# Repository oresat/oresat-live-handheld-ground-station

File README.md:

# Introduction
The OreSat Live Handheld Ground Station (HGS) project provides everything you need to build your own ground station capable of receiving images transmitted from OreSat in Low Earth Orbit.  HGS is designed to be inexpensive, easy to assemble, and simple to use so that it can be built by Middle and High School students.  The entire design is open source to encourage reuse and experimentation.

HGS is a portable unit built around a high gain directional antenna. Using a mobile phone application to locate OreSat, you aim the antenna to get the best possible signal. The live images are then received by the groundstation, error corrections are applied and the image is made available to any WiFi capable device through a built-in web page.

OreSat HGS act as a wifi access point providing an unsecured wireless network named "OreSatLive".  Devices identify the network as a hotspot requiring the user to sign-in for Internet access.  To view the image stream simply:
1. Connect your wifi to the "OreSatLive" network
2. Choose to sign-in when prompted
3. The OreSat Live web interface will open automatically

HGS was created for use with the OreSat mission, but it is designed to be used by any group interested in long range image transmission.  The handheld ground stations can be reused for other cubesat or balloon launches.

Once the final design is completed, users will be able to purchase all of the required parts as a kit from https://www.crowdsupply.com/

# HGS Parts List
All of the required parts to build HGS can be found in the Bill of Materials [(BOM)](BOM.md)

# Hardware Setup
Build your Handheld Ground Station kit according to the [Assembly Instructions](hgs-model/assembly-instructions/OreSat_Live_HGS_Assembly.pdf)

# Software Setup
1. [Download the SD card image oresat_hgs_14_jun_2019.img](https://drive.google.com/a/pdx.edu/uc?id=1BvP8ltkEwoBRSbCfQXceEiuxpVhkSf37&export=download)
2. Write the SD card image to a 2GB or larger card.  The [Raspberry Pi documentation](https://www.raspberrypi.org/documentation/installation/installing-images/) explains the procedure.

# Startup Procedure
1. Install the SD card in Raspberry Pi
2. Insert phone into the holder
3. Connect Raspberry Pi power cable to the USB power bank
4. Load Satellite AR app on phone and select OreSat
5. Point the ground station in the direction of OreSat
3. Connect your viewing devices to the "OreSatLive" wifi network

# Design Details
## Software Design
If you would like to build the software system from source follow the [Build Instructions](software/BUILD.md)

## Mechanical Design
You can 3D print all of the [mechanical parts](hgs-model/README.md)  

## Circuit Board Design
The integrated antenna backplane and matching network [circuit board design files](backplane/README.md)

# Related Projects
[OreSat Live](https://github.com/oresat/oresat-dxwifi-software) for software and firmware used on OreSat satellite

[Mini OreSat](https://github.com/oresat/oresat-live-mini-oresat) combines the OreSat Live software with a Raspberry Pi Zero W + Pi Camera to create platform for hobbyist and classroom experiments with high-altitude ballooning.

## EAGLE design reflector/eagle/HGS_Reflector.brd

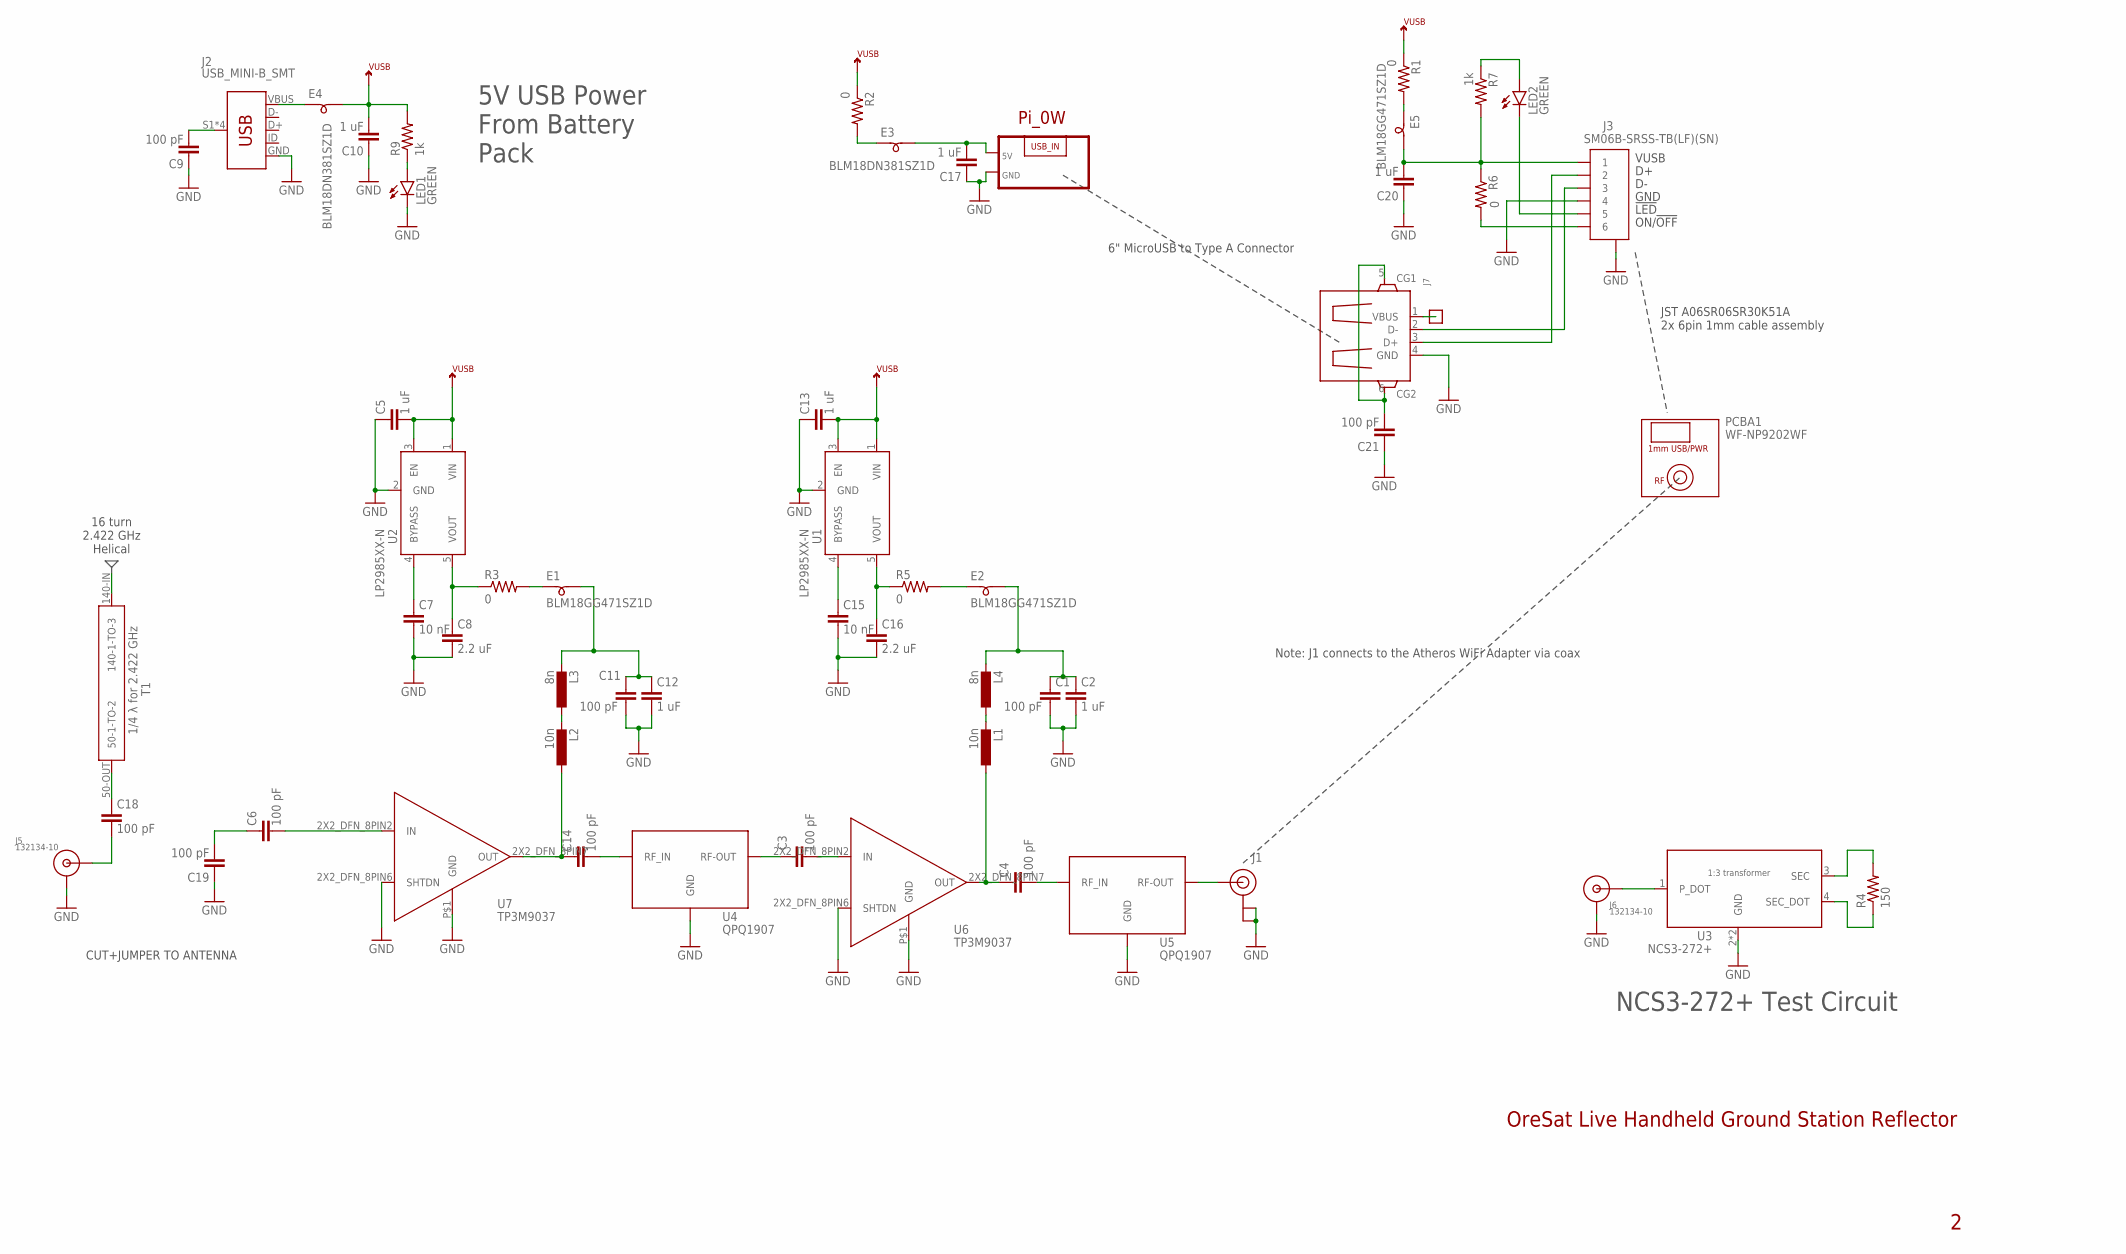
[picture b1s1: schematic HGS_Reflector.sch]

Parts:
C1, C9, C11, C21: 100 pF; .0603-C-NOSILK
C2, C12: 1 uF; .0603-C-NOSILK
C3, C4, C6, C14, C18, C19: 100 pF; .0402-C-NOSILK
C5, C10, C13, C17, C20: 1 uF; .0603-B-NOSILK
C7, C15: 10 nF; .0603-B-NOSILK
C8, C16: 2.2 uF; .0603-B-NOSILK
E1, E2, E5: BLM18GG471SZ1D; .0603-B
E3, E4: BLM18DN381SZ1D; .0603-B
J1: U.FL
J2: USB_MINI-B_SMT; USB-MINIB
J3: SM06B-SRSS-TB(LF)(SN); CONN_SM06B-SRSS-TB_JST
J5, J6: 132134-10
J7: USB_HOST_W/CHASSIS_GND; GHI2_USB_HOST_HORIZONTAL_W/CHASSIS_GND
L1, L2: 10n; L3216C
L3, L4: 8n; L3216C
LED1, LED2: GREEN; LED-0603
PCBA1: WF-NP9202WF; WF-NP9202
PCBA2: RASP_PI_0WPI_0W; RASP_PI_0W
R1, R2, R3, R5, R6: 0; .0603-B-NOSILK
R4: 150; .0402-C-NOSILK
R7, R9: 1k; .0603-B-NOSILK
T1: QWT2.4222; QWT_2.422G-V2
TP2: TEST-POINT-LARGE-SQUARE; 1X01
U1, U2: LP2985XX-N; SOT-23
U3: NCS3-272+; GE0805C-1
U4, U5: QPQ1907
U6, U7: LNA-TP3M9037; TP3M9037

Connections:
GND: C1.2, C2.2, C5.1, C7.2, C8.2, C9.1, C10.1, C11.2, C12.2, C13.1, C15.2, C16.2, C17.1, C19.1, C20.1, C21.1, J1.1 (GND), J1.2 (GND), J2.GND, J3.4, J3.7, J3.8 (7), J5.SHIELD (GND), J6.SHIELD (GND), J7.4 (GND), LED1.C, PCBA2.GND, U1.2 (GND), U2.2 (GND), U3.2 (GND), U3.5 (GND), U4.GND, U4.GND2 (GND), U4.GND3 (GND), U5.GND, U5.GND2 (GND), U5.GND3 (GND), U6.2X2_DFN_8PIN6 (SHTDN), U6.P$1 (GND), U7.2X2_DFN_8PIN6 (SHTDN), U7.P$1 (GND)
HELICAL: T1.140-IN (140-1-TO-3)
unnamed: C7.1, U2.4 (BYPASS)
unnamed: E1.1, R3.2
unnamed: C4.2, U5.INPUT (RF_IN)
unnamed: C3.1, U4.OUTPUT (RF-OUT)
unnamed: J1.FEED (SIGNAL), U5.OUTPUT (RF-OUT)
unnamed: C14.2, U4.INPUT (RF_IN)
unnamed: L2.2, L3.1
unnamed: C3.2, U6.2X2_DFN_8PIN2 (IN)
unnamed: E2.1, R5.2
unnamed: LED1.A, R9.1
unnamed: C6.2, U7.2X2_DFN_8PIN2 (IN)
unnamed: C9.2, J2.S1 (SHIELD), J2.S2 (SHIELD), J2.S3 (SHIELD), J2.S4 (SHIELD)
unnamed: C4.1, L1.1, U6.2X2_DFN_8PIN7 (OUT)
unnamed: L1.2, L4.1
unnamed: C17.2, E3.2, PCBA2.5V
unnamed: C14.1, L2.1, U7.2X2_DFN_8PIN7 (OUT)
unnamed: E4.1, J2.VBUS
unnamed: E3.1, R2.2
unnamed: C15.1, U1.4 (BYPASS)
unnamed: C11.1, C12.1, E1.2, L3.2
unnamed: C1.1, C2.1, E2.2, L4.2
unnamed: C16.1, R5.1, U1.5 (VOUT)
unnamed: C18.2, J5.CENTER (SIG)
unnamed: J6.CENTER (SIG), U3.1 (P_DOT)
unnamed: C8.1, R3.1, U2.5 (VOUT)
unnamed: R4.2, U3.3 (SEC)
unnamed: R4.1, U3.4 (SEC_DOT)
unnamed: C6.1, C19.2
unnamed: C20.2, E5.2, J3.1, R6.1, R7.2
unnamed: E5.1, R1.2
unnamed: J3.6, R6.2
unnamed: LED2.A, R7.1
unnamed: J3.2, J7.3 (D+)
unnamed: J3.5, LED2.C
unnamed: J3.3, J7.2 (D-)
unnamed: J7.1 (VBUS), TP2.1
unnamed: C21.2, J7.5 (CG1), J7.6 (CG2)
T1-50: C18.1, T1.50-OUT (50-1-TO-2)
VUSB: C5.2, C10.2, C13.2, E4.2, R1.1, R2.1, R9.2, U1.1 (VIN), U1.3 (EN), U2.1 (VIN), U2.3 (EN)

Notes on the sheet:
OreSat Live Handheld Ground Station Reflector
Note: J1 connects to the Atheros WiFi Adapter via coax
16 turn 2.422 GHz Helical
NCS3-272+ Test Circuit
5V USB Power From Battery Pack
CUT+JUMPER TO ANTENNA
VUSB
GND
!LED
ON/!OFF
JST A06SR06SR30K51A 2x 6pin 1mm cable assembly
6" MicroUSB to Type A Connector

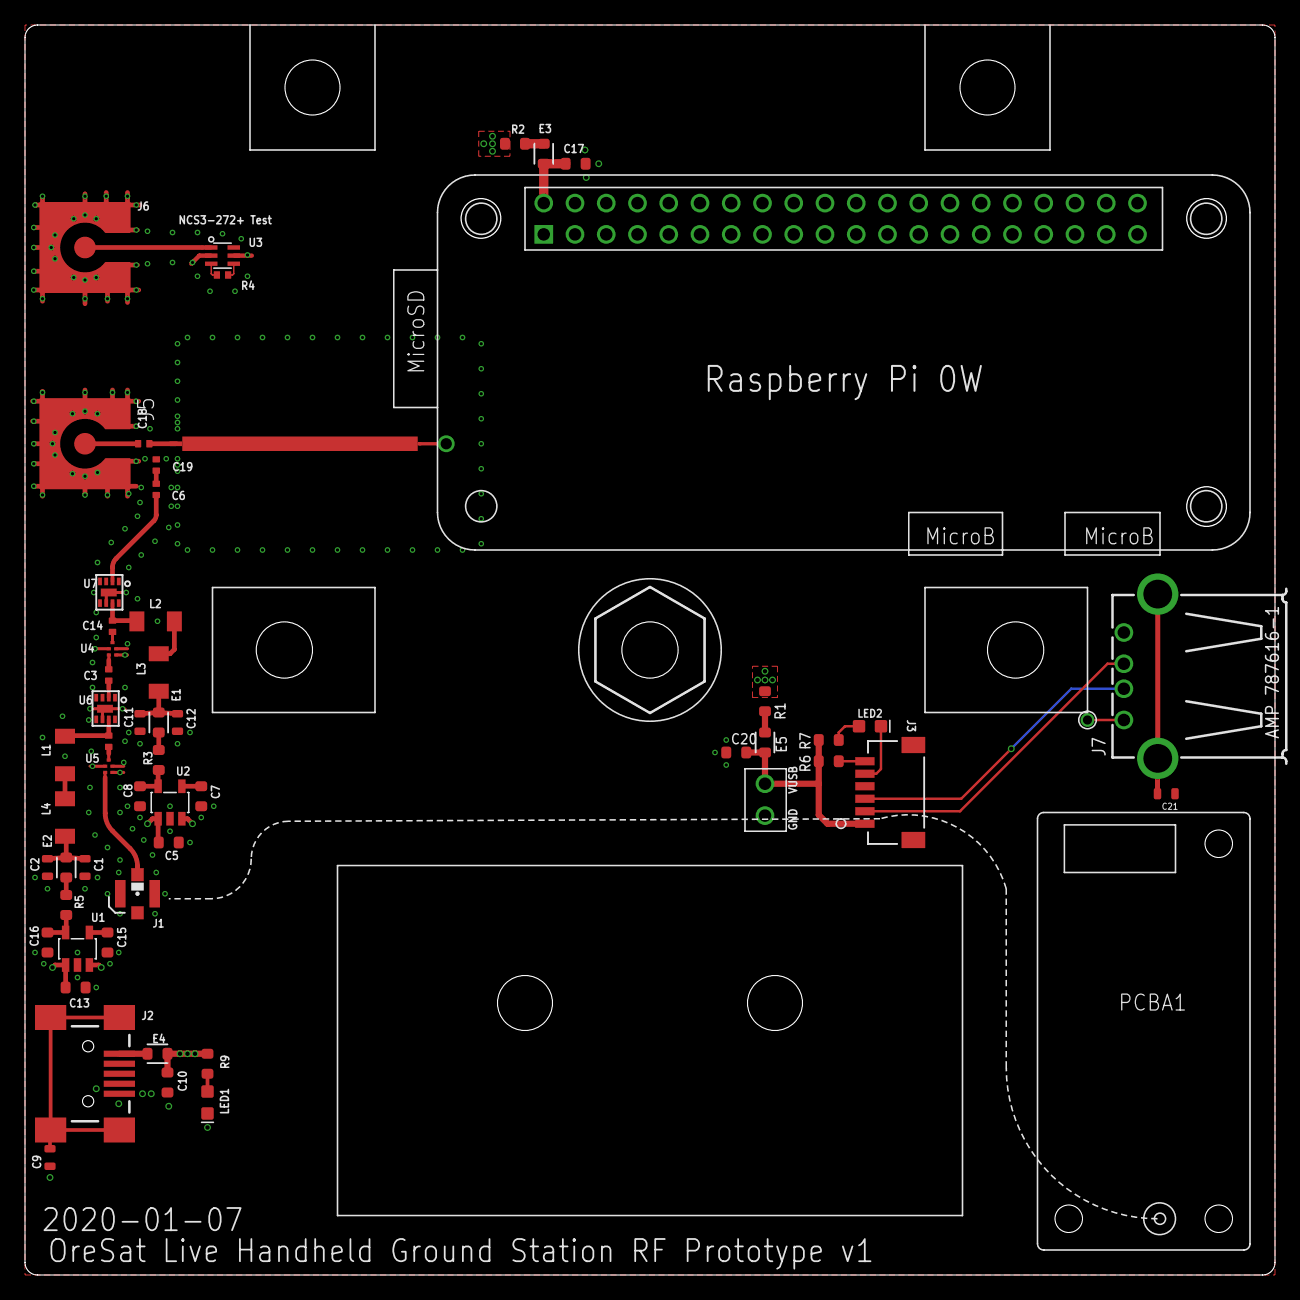
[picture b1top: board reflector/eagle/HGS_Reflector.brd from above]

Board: 4 copper layers, 100.0 x 100.0 mm, 57 parts (0 on the bottom side), 40 nets.

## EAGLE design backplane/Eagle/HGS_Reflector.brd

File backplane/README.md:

# Backplane for Handheld Ground Station
Schematic files for the backplane, including impedence matching circuit for connecting the antenna to the rest of the components.

Schematic files created using KiCad 5.1.2.
- **.pro** to open up Kicad project
- **.kicad_pcb** for the PCB layout
- **.kicad_mod** for the individual footprints

Backplane material: FR-4 PCB material, 0.5 oz copper, 1.58 mm thick, Er 4.34 @ 1 GHz

### Microstrip/transformer notes
Microstrip dimensions:
- Width:	1.20938 mm
- Length:	17.7623 mm

For signal lines to and from microstrip:
```
50 ohm
	Width:  3.05184 mm
	Length: Arbitrary

140 ohm
	Width:  0.238155 mm
	Length: Arbitrary
```
### Other notes
[Source for Raspberry Pi Zero footprint dimensions](http://www.electronics-lab.com/raspberry-pi-zero-footprint-and-dimensions/)\
[Source for wf-np9202 footprint dimensions](https://www.aliexpress.com/item/wireless-net-card-LAN-NIC-module-AR9271-150M-wireless-LAN-net-card-industrial-module/32746090657.html?tt=sns_none&aff_platform=default&cpt=1557507604073&sk=cC0ydLx2&aff_trace_key=5d988d9ac55b4f4d80da408161a19463-1557507604073-02869-cC0ydLx2&terminal_id=523d634d52754e72ad5634ec5f8829c2)

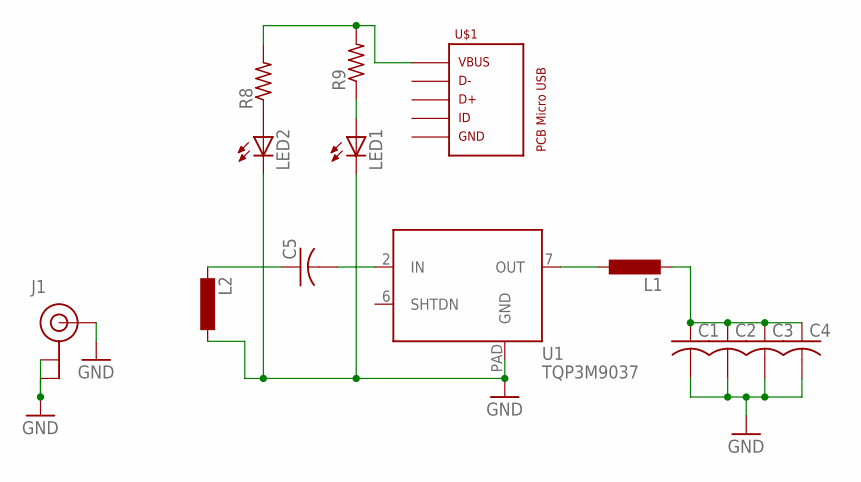
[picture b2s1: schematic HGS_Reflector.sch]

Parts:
C1, C2, C3, C4, C5: C-USC1210; C1210
J1: U.FL
L1, L2: L-EUL3216C; L3216C
LED1, LED2: LED_E; LED_1206
R8, R9: R-US_R0402; R0402
U1: TQP3M9037; DFN8-2X2-WITH-PAD
U$1: PCB_MICRO_USB_BSS_1; USB_TYPE_B_SS_1

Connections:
GND: C1.2, C2.2, C3.2, C4.2, J1.1 (GND), J1.2 (GND), J1.FEED (SIGNAL), L2.1, LED1.C, LED2.C, U1.PAD (GND)
unnamed: L1.1, U1.7 (OUT)
unnamed: C1.1, C2.1, C3.1, C4.1, L1.2
unnamed: C5.1, L2.2
unnamed: C5.2, U1.2 (IN)
unnamed: LED2.A, R8.1
unnamed: LED1.A, R9.1
unnamed: R8.2, R9.2, U$1.1

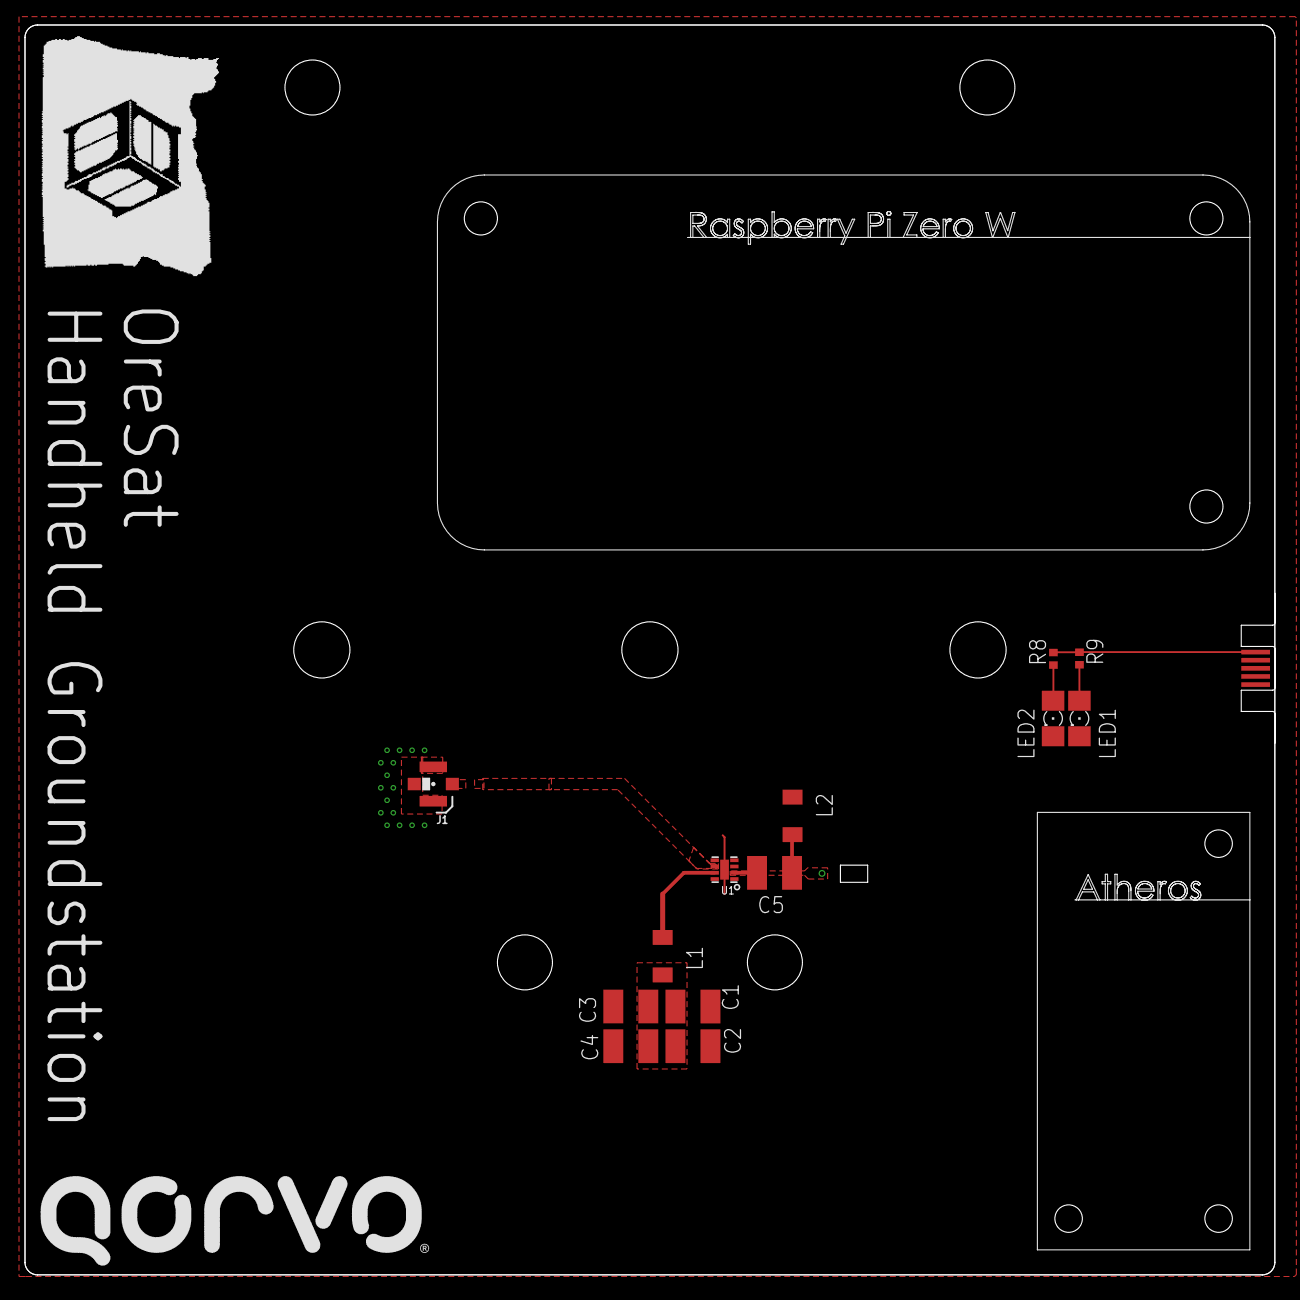
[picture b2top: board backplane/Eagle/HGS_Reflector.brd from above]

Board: 4 copper layers, 100.0 x 100.0 mm, 14 parts (0 on the bottom side), 8 nets.

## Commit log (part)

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2019-02-11 Added antenna segment 3d print files.
    Added the SLDPRT and STL files of the helical antenna (initial version). Also added initial version of README files for the associated folders.
2019-02-11 Improved helical antenna 3d model to disallow incorrect assembly
    Converted a peg to a 'key' peg to disallow incorrect rotation.
2019-02-26 Reorganized 3d model folders, changed antenna pegs to square.
    Reorganized 3D models into one folder, with added documentation, to support a mockup assembly.
    Replaced previous three round pegs with a single square peg with an alignment peg attached to one side. Should allow for a single top cap that can be attached in four orientations for the 4 antenna a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
2019-03-26 Uploaded ap mode setup script for raspberry pi
2019-04-14 Added basic simple HTML page for livestream
2019-04-14 Changed body text color to contrast background
2019-04-14 Changed color of overlay text to green
2019-04-19 Added latest streaming method with pause button
2019-04-24 Removed tabs and adjusted holes for #4 screws
2019-04-24 Started KiCad project for backplane
2019-04-27 Handle model: smoothed edges, added 1/4-20 nut slot for mounting, etc.
    Added screw insets for the clamp.
    Added exported model for printing.
2019-04-27 Antenna_endcap: changed name to "Antenna_Base_Clamp", etc
    Made clamp tighter (to size of peg without extra clearance.)
    Added .stl for printing.
2019-04-27 Added fastener dimensions to documentation. Edited handle to match.
2019-04-27 Phone_Clamp_base: Moved holes in, extended slots, clamp: Moved holes in
2019-04-29 Made most of the backplane design, no idea if it'll actually work
    Missing impedance matching bit
2019-04-29 Added new display section for useful times
    Local time is no longer over streaming images.
2019-04-29 Moved javascript to separate files to clean HTML
2019-04-29 Cleaned up method for blinking colons for times
2019-04-29 Added placeholder altitude
    Also some minor change to displaying values for the table with
    AOS and LOS.
2019-04-30 Fixed reference to footprint library location
2019-05-01 Adjusted backplane layout
2019-05-01 Added gerber files to use with router
2019-05-01 Updated footprint and PCB layout
    Accidently undid a new through-hole in last commit.
    Updated footprint for microstrip to include clearance.
2019-05-08 Updated microstrip and moved components around
    Microstrip now has solder mask on the tips for soldering wires to it,
    and holes nearby for connecting coax cable and antenna.
    RPi and WiFi module mount holes have been moved to match first prototype
    assembled for open house.
2019-05-09 Updated silkscreen and REF values for footprints
    Footprints now have unique names for easy reference in library.
    Names for footprints have been moved around so that they don't overlap
    on PCB layout.
    Labels for RPi Zero connections moved outside box for visibility when
    RPi is mounted onto backplane.
2019-05-09 Added version number in silkscreen
2019-05-09 Updated Phone holder base to 3.2mm holes and slots
2019-05-09 Updated handle clamp to 3.2mm holes
2019-05-09 Added OreSat logo to silkscreen
    Included dxf version of logo needed to import to Kicad
    Added logo as footprint (includes version number)
2019-05-10 Updated footprint for Raspberry Pi Zero
2019-05-13 Added holes for strings and modified microstrip
    Board layout now reflects what users see when using the product from the
    back of the board. The side of the microstrip where the antenna will feed
    in now has a rectangular hole.
2019-05-13 Added ground planes and vias
2019-05-16 Antenna base clamp: made slightly thicker
2019-05-16 Handle: suppressed features, shortened handle (reverting to no battery)
    Suppressed USB slot
    Suppressed battery compartment
    Shortened handle back to previous length for more solid assembly
    Made bolt holes slightly larger
    Chamfered bolt head insets for printing
    Filleted handle top corners
2019-05-16 Phone holder base: Chamfered bolt head insets, Enlarged bolt holes
2019-05-16 Helical antenna segment: enlarged wire attachment loop
2019-05-25 Adding major changes to transformer and others
    Moved Atheros module out from under phone clamp for easier assembly.
    Slot for antenna wire to feed through is now a edge cut.
    Through-hole to GND plane on opposite end of transformer is now a SMD for
    a UFL connector.
    Transformer clearance is now a copper trace isolating the microstrip.
2019-05-26 Changed antenna feed slot width to be 1.5mm and other
    Cleaned up floating unnecessary silkscreen
    Removed solder mask for mounting holes
    Updated version number text for HGS
2019-05-28 Updated standard to M3.5/#6 bolts
2019-05-28 Handle/split handle: updated fastener sizes to new standard
    Also enlarged standard sizes slightly
2019-05-28 Readme: changed standard to next size of bolt up, M3.5 to M4
    Hopefully easier to find.
2019-05-28 Handle_Clamp: Updated to M4
2019-05-28 Added new model phone and battery holder bottom section
2019-05-28 Added base section of new Phone and battery holder design
2019-05-29 Replaced transformer isolation with "Keep Out" zones
    Was previously using a copper trace to isolate the transformer to prevent
    copper fill to get around it. Found keep out zone option to define areas
    that we don't want copper to be in.
2019-06-02 Adding major final changes for transformer strip
    Moved transformer parts closer to antenna by 1mm
    Transformer microstrip reverted to original intended size
    Added footprint for 0402 capacitor to replace gap between U.FL and strip
    Modified U.FL footprint pads to be "solid" to allow for copper fill to
    connect to the GND pads
    Phone Clamp and Handle mount holes changed to 4.5mm
2019-06-02 Phone&Battery_Holder_Base: moved holes out to the sides and longer legs
    Also thinner body
2019-06-02 Handle: Increased clamp base thickness to match phone&battery holder
2019-06-02 Phone&Battery_Holder: Lots of changes to fit together better&new battery
    Bottom: added slot for Top and extended battery section for new battery spec
    Top: Lengthened base to fit along Bottom for much larger range of phone sizes
2019-06-02 Antenna_Base_Clamp: added roof and bolt hole and inset
2019-06-02 Antenna_Cap: Added bolt hole and hex inset
2019-06-06 Changed velocity units to metric
    Was mph. Is now km/h
2019-06-13 Updated README formatting for markdown
2019-06-13 Added section titles to backplane README
    Also added descriptions of important Kicad files
2019-06-20 Restructure files and improve documentation
2019-06-21 Added assembly instructions PDF and source Latex
    README link has been linked to go straight PDF
2019-06-21 Removed Kicad temp and unecessary files
    Added gitignore to prevent pushes of temp files
2019-07-16 updated antenna segments
2019-07-17 asjkdfnajks
2019-07-19 updated antenna stuff
2019-07-24 updated antenna, added build folder for STLs
2019-07-26 updated hgs assembly
2019-08-12 updated CAD assembly and added screenshots
2019-08-12 started translating board files from heathenous Kicad to gloroius eagle
2019-08-13 updated bill of materials
2019-08-13 handheld ground station eagle mockup
2019-08-13 updated hgs mockup
2019-08-15 updated rubber band holding parts and their STLs
2019-08-20 "auto-generated from update_repos.py"
2019-12-05 updated battery holder for velcro location. updated groundplane with keepout locations and dxf
2020-01-08 added STLs of the current CAD
2020-04-17 Archived kicad files, added right design rules to EAGLE files.
2020-05-07 updated HGS exploded view
2020-05-12 Small reorganization, it's reflector not backplane. Updated DXF layer for latest MCAD. After discussion, decided to move LNA and all sensitive parts to the top of the board which is now the helical s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
2020-07-13 Updated handheld. Increased number of segments, extended rod.
2020-07-19 removed temp files
2020-08-02 Completed schematic with respect to the current block diagram
2020-08-02 Fixed USB pin issue
2020-08-16 Schematic, board and BOM updates
2020-08-18 Correcting the file name for the BOM
2020-08-20 I've completed the BOM for version 1 of the PCB for the reflector. Regarding the board and schematic themselves, the board needs to be mapped out with all parts oriented before being reviewed.
2020-10-06 Fixed a bad cut.
2020-10-18 I completed the physical layout of the board for HGS. Currently, I just need to sort through some DRC errors that I don't know how to fix, and do a design review.
2020-11-15 I incorporated the 1/4 wave transformer part (TM-QWT-2.422GHz.lbr) into the HGS reflector board, but I have not yet consulted with the person who designed the part in order to situate it properly.
2020-11-22 I continued optimizing the trace lengths for the parts on the HGS board, but have not yet been able to situation the 1/4 wave transformer part on the ground plane with the other parts.
2020-11-22 Updated CAD to work with new helical dimensions
2020-11-29 Since the team working on HGS decided to switch from a 2 layer board to a 4 layer board, I began laying out the HGS parts on a new board with 4 layers. Currently, I have a number of questions regardi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
2020-12-02 Updated CAD
2020-12-06 Fixed hex trap CAD
2020-12-06 Last Thursday, I updated the HGS board to its actual shape by importing the the DXF file that Marvin Lin sent me. I began work on re-routing the board to fit within the DXF dimensions.
2020-12-12 With the DXF layer properly configured, I positioned all parts onto the board and completed all of the routing. However, there are a few DRC issues involving details of footprints that need to be cha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
2020-12-13 I made sure that all the signals were completely routed, and fixed the clearance issue with the wire going to the center by replacing the center drill hole with a large via that goes directly to the 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
2020-12-22 Fixed tolerance issue with hex trap and various other parts
2020-12-23 I finalized the schematic and routing of the board for HGS. Note that I adjusted the dxf layer by adding a fourth drill hole underneath the atheros card. It is ready for a design review.
2020-12-23 Added antenna side DXF and fixed broken assembly relations
2020-12-25 After connecting the Pi 0W footprint to the ground plane, I fixed the issue of the Pi 0W pin header floating.
2020-12-27 Removed script.
2021-01-04 Update for Oliver's series of RF tests to see if we can really do this HGS thing. Took Nohl's board and cleaned it up a bit; the LNA and PS and other things are just for fun; the real purpose of this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
2021-01-07 Switched edge fired SMA connectors to Oliver's fancy SMT vertical connectors.
2021-01-08 Part and BOM cleanup
2021-01-24 I made a few additions to the HGS BOM before Oliver Jones made a new BOM.
2021-05-24 Modified design for antenna pitch of 28.6mm and diameter of 43mm
2021-11-13 Added depression for new feed system
2022-02-07 NICK!!!!
    Learned that KiCad needs the .wks file
2022-04-18 transformer test board
    test board for 3:1 balun transformer
2022-04-21 Fixed .gitignore for KiCAD 6, removed backups and other temp files, updated board file with 4 layer oshpark from the oresat-kicad repo, moved antenna much closer to the transformer and reduced the tr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
2022-04-21 Added kicad submodule
2022-04-21 Updated .gitignore.
2022-04-21 Sent off for Fab, v1.0
    Updated libraries and library paths; might actually not be terrible now with the submodule? Fixed footprint of transformer and rotated 90 degrees; made board OCD compliant and did via cleanup.
2022-04-21 Updated library paths to be more sane, especially for footprints. Then unmasked the vias along the edges so that we can get castellated edges. Also reduced the size of the antenna hole, no reason to 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
2022-04-22 Added datasheets to symbols, and 3D model of SMA connector to PCB
2022-04-29 LNA Board
    LNA test board with both stages. Has ability to test each stage.
2022-05-01 LNA
    Fixed minor issues in RF path.
2022-05-05 LNA Board
    LNA Test board with ability to test each stage
2022-05-12 LNA Test Board
    PCB to test each stage ofthe HGS LNA
2022-05-23 LNA BOM added
    BOM of LNA test board
2022-07-10 fixed microstrip width and moved SMA away from R1
2022-07-10 pulled away the solder mask from the transmission line
2022-07-10 pulled refdes's away from stiching
2022-10-30 LNA Test Board
    Reviewed work done during capstone. Everything seems ready to build and test.
2023-02-09 50 Ohm microstrip
    Test boards with a through, impedance matching network and 50ohm load test
2023-05-14 Matching Board with open stub
    Added extra vias around pads
2023-05-25 Reduced SMA GND pin thermal relief
    Reduced SMA GND pin thermal relief also noticed a few pads not connected to GND net
2023-05-26 Fixed issues with backside SMA connector GND pins
    backside GND pins had not net. Connected them to GND net
2023-05-26 Better .gitignore file.
2024-09-11 deleted temp files
2024-09-13 fixed reference designators, fixed symbol/footprint pads and pins, added impedance matching at helical

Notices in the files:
parts and their libraries:
SparkFun-Connectors: Licensing: Creative Commons ShareAlike 4.0 International - https://creativecommons.org/licenses/by-sa/4.0
COPYRIGHT: Copyright (C) 2018 Accelerated Designs. All rights reserved
